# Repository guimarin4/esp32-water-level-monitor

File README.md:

# ESP32 Water Level Monitor

IoT-based water tank level monitoring system using an ESP32 DevKit V1 and a waterproof JSN-SR04T ultrasonic sensor.

The project aims to measure the water level of a tank, filter measurement noise, and provide real-time monitoring through a local web dashboard.

## Project Status

Current development stage:

* [x] ESP32 board testing
* [x] JSN-SR04T wiring
* [x] Basic ultrasonic sensor test
* [ ] Sensor reading validation
* [x] Median filtering of valid samples
* [x] Water level percentage calculation
* [x] Wi-Fi connectivity
* [x] Local web server
* [x] AJAX/JSON real-time dashboard
* [x] Invalid readings and missing echoes handled
* [ ] Optional MQTT integration
* [ ] Optional LoRa communication

## Hardware

* ESP32 DevKit V1
* JSN-SR04T waterproof ultrasonic sensor
* 1 kΩ resistor
* 2 kΩ resistor
* Jumper wires
* USB power supply
* Water tank

## Tank Parameters

| Parameter           |  Value |
| ------------------- | -----: |
| Full tank distance  |  15 cm |
| Empty tank distance |  45 cm |
| Water height        |  30 cm |

These are the current firmware calibration values. The provisional minimum sensor
distance is 25 cm; confirm it against the exact module's datasheet. With the
current 15 cm full-tank distance, the upper part of the water level is outside
the accepted range (the highest accepted level is about 66.7%). Reposition the
sensor with clearance above its minimum range at full tank, then update
`DISTANCIA_CHEIA` to the actual distance. Keep `ALTURA_AGUA` equal to the actual
usable water height. The dashboard and serial output warn about this mismatch.

## Measurement Behavior

* During testing, a group of five samples is collected every two seconds, with
  at least 70 ms between triggers. Email sending is disabled.
* Samples outside `DISTANCIA_MIN_SENSOR` through `DISTANCIA_VAZIA + 5 cm`,
  including missing echoes, are discarded. At least three valid samples are
  required; their median determines distance, height, and level.
* An invalid group preserves the last valid values and their original timestamp.
  The dashboard marks them as outdated. Before the first valid reading, it shows
  placeholders. Invalid readings never imply that the tank is full.
* Wi-Fi startup waits at most ten seconds. Measurements continue through the
  serial port when offline, and Wi-Fi reconnection is attempted every 30 seconds.

The filter reduces isolated spikes; persistent incorrect echoes inside the
accepted range can still affect measurements. Validate the installation at both
full and empty tank, with a clear path from the sensor face to the water.

## Verification

Build the firmware with `pio run`. The filter and dashboard tests can also run
without the ESP32. With a native C++ compiler and Node.js installed, run from the
project directory in PowerShell:

```powershell
g++ -std=c++11 -Wall -Wextra -Werror -I include test/test_measurement.cpp -o "$env:TEMP\water-monitor-filter-test.exe"
& "$env:TEMP\water-monitor-filter-test.exe"
node test/test_dashboard.js
```

## Pin Connections

| JSN-SR04T | ESP32                           |
| --------- | ------------------------------- |
| VCC       | 5V / VIN                        |
| GND       | GND                             |
| TRIG      | GPIO 5                          |
| ECHO      | GPIO 18 through voltage divider |

> Important: the JSN-SR04T ECHO output can operate at 5 V, while the ESP32 GPIO operates at 3.3 V. A voltage divider is therefore used between the ECHO pin and GPIO 18.

## Future Improvements

Possible future improvements include:

* MQTT integration
* Home Assistant integration
* Low-level alerts
* Historical data logging
* LoRa communication for remote installations
* OLED local display
* Battery or solar-powered operation

## License

This project is released under the MIT License.

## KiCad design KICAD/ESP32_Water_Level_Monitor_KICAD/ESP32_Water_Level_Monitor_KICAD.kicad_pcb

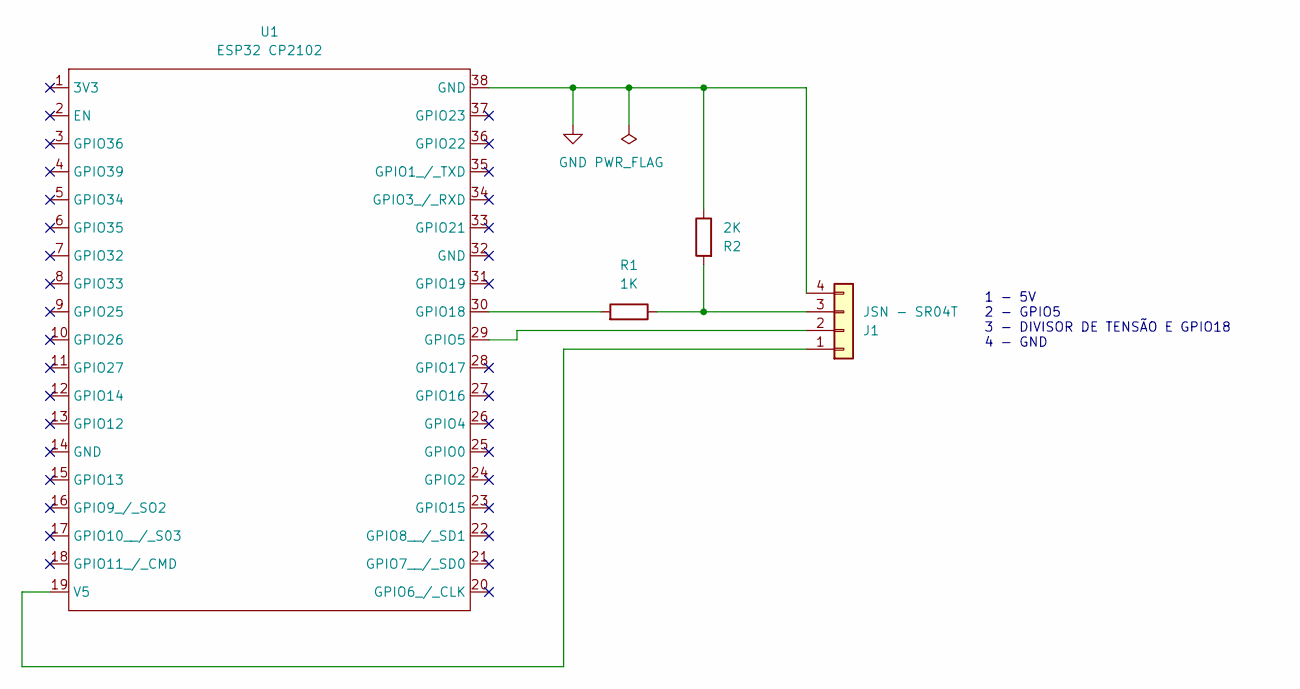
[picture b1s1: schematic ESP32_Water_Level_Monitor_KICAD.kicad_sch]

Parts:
J1: JSN - SR04T; PinHeader_1x04_P2.54mm_Vertical
R1: 1K; R_Axial_DIN0204_L3.6mm_D1.6mm_P1.90mm_Vertical
R2: 2K; R_Axial_DIN0204_L3.6mm_D1.6mm_P1.90mm_Vertical
U1: ESP32 CP2102; ESP32_38Pin

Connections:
GND: J1.4, R2.1, U1.38 (GND)
unnamed: J1.1, U1.19 (V5)
unnamed: J1.2, U1.29 (GPIO5)
unnamed: J1.3, R1.1, R2.2
unnamed: R1.2, U1.30 (GPIO18)

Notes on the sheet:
1 - 5V 2 - GPIO5 3 - DIVISOR DE TENSÃO E GPIO18 4 - GND

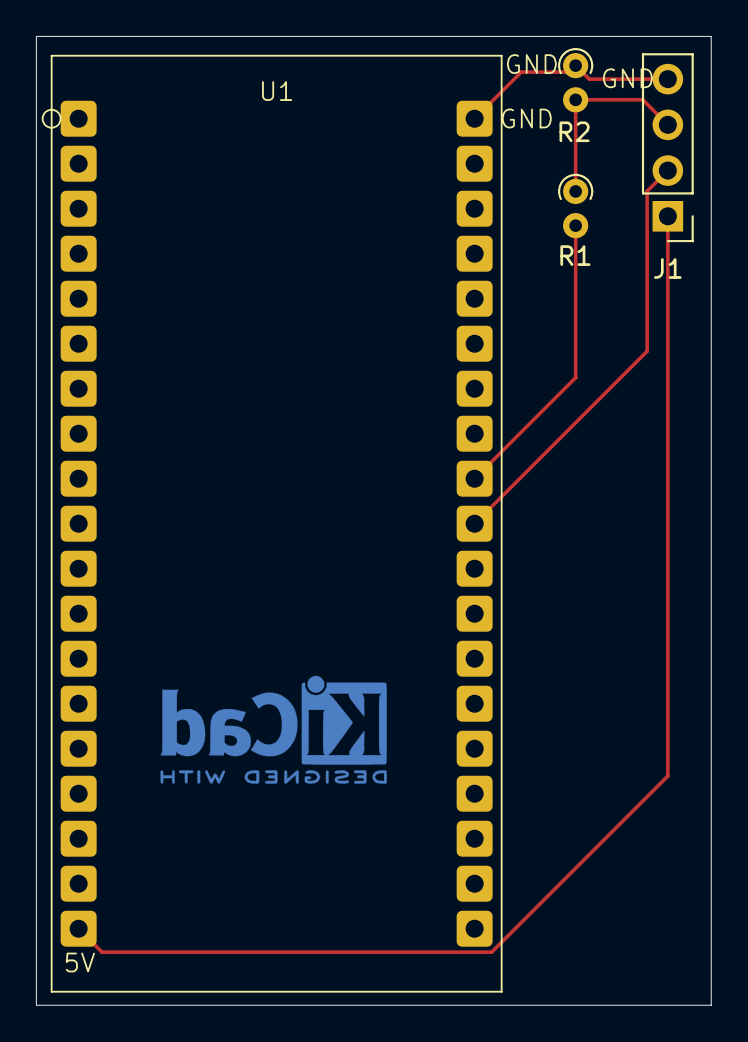
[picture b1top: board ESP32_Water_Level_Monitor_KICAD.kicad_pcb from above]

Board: 2 copper layers, 37.5 x 53.8 mm, 4 parts (0 on the bottom side), 5 nets.
